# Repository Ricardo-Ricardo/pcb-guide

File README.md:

# pcb-guide
 first keyboard pcb

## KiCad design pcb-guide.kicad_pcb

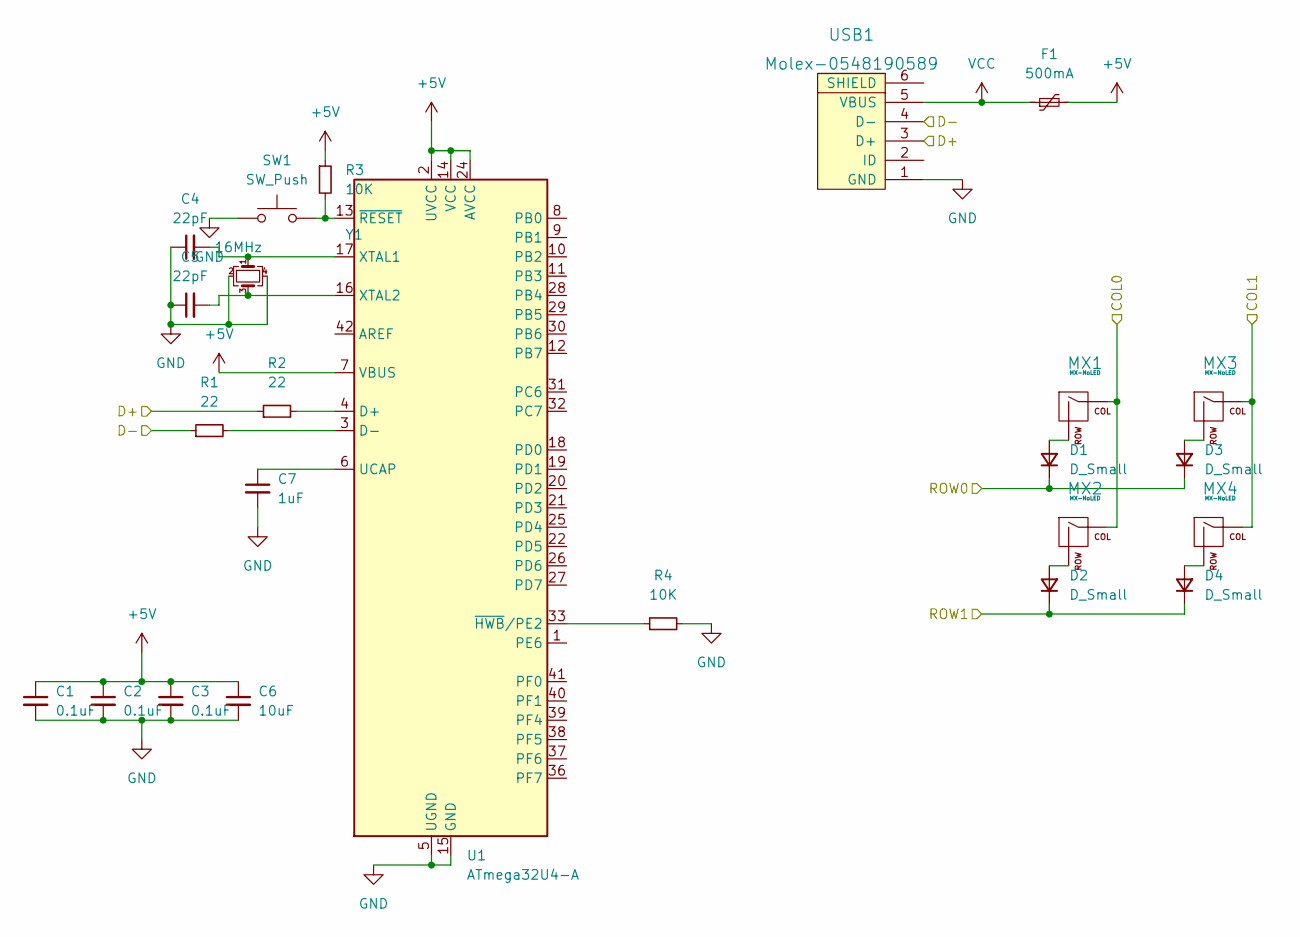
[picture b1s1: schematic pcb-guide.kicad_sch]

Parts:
C1, C2, C3: 0.1uF; C_0805_2012Metric
C4, C5: 22pF; C_0805_2012Metric
C6: 10uF; C_0805_2012Metric
C7: 1uF; C_0805_2012Metric
D1, D2, D3, D4: D_Small; D_SOD-123
F1: 500mA; Fuse_1206_3216Metric
MX1, MX2, MX3, MX4: MX-NoLED; MX-1U
R1, R2: 22; R_0805_2012Metric
R3, R4: 10K; R_0805_2012Metric
SW1: SW_Push; SKQG-1155865
U1: ATmega32U4-A; TQFP-44_10x10mm_P0.8mm
USB1: Molex-0548190589
Y1: 16MHz; TQFP-44_10x10mm_P0.8mm

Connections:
+5V: C1.1, C2.1, C3.1, C6.1, F1.2, R3.1, U1.2 (UVCC), U1.7 (VBUS), U1.14 (VCC), U1.24 (AVCC), U1.34 (VCC), U1.44 (AVCC)
/COL0: MX1.1 (COL), MX2.1 (COL), U1.29 (PB5)
/COL1: MX3.1 (COL), MX4.1 (COL), U1.28 (PB4)
/D+: R2.1, USB1.3 (D+); also elsewhere on the board
/D-: R1.1, USB1.4 (D-); also elsewhere on the board
/ROW0: D1.1 (K), D3.1 (K), U1.27 (PD7)
/ROW1: D2.1 (K), D4.1 (K), U1.30 (PB6)
GND: C1.2, C2.2, C3.2, C4.1, C5.1, C6.2, C7.2, R4.2, SW1.1, U1.5 (UGND), U1.15 (GND), U1.23 (GND), U1.35 (GND), U1.43 (GND), USB1.1 (GND), Y1.2, Y1.4; also elsewhere on the board
unnamed: C4.2, U1.17 (XTAL1), Y1.1
unnamed: C5.2, U1.16 (XTAL2), Y1.3
unnamed: C7.1, U1.6 (UCAP)
unnamed: D1.2 (A), MX1.2 (ROW)
unnamed: D2.2 (A), MX2.2 (ROW)
unnamed: D3.2 (A), MX3.2 (ROW)
unnamed: D4.2 (A), MX4.2 (ROW)
unnamed: R1.2, U1.3 (D-)
unnamed: R2.2, U1.4 (D+)
unnamed: R3.2, SW1.2, U1.13 (~RESET)
unnamed: R4.1, U1.33 (~HWB/PE2)
VCC: F1.1, USB1.5 (VBUS); also elsewhere on the board

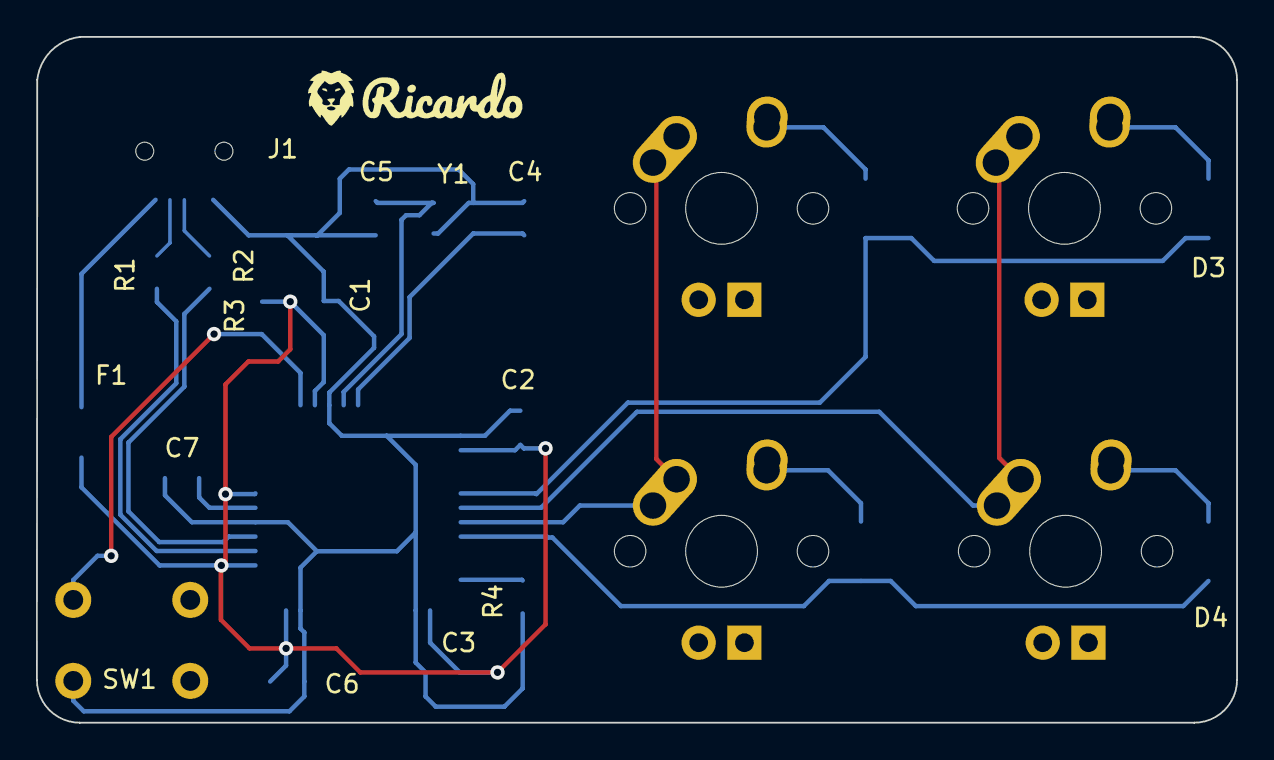
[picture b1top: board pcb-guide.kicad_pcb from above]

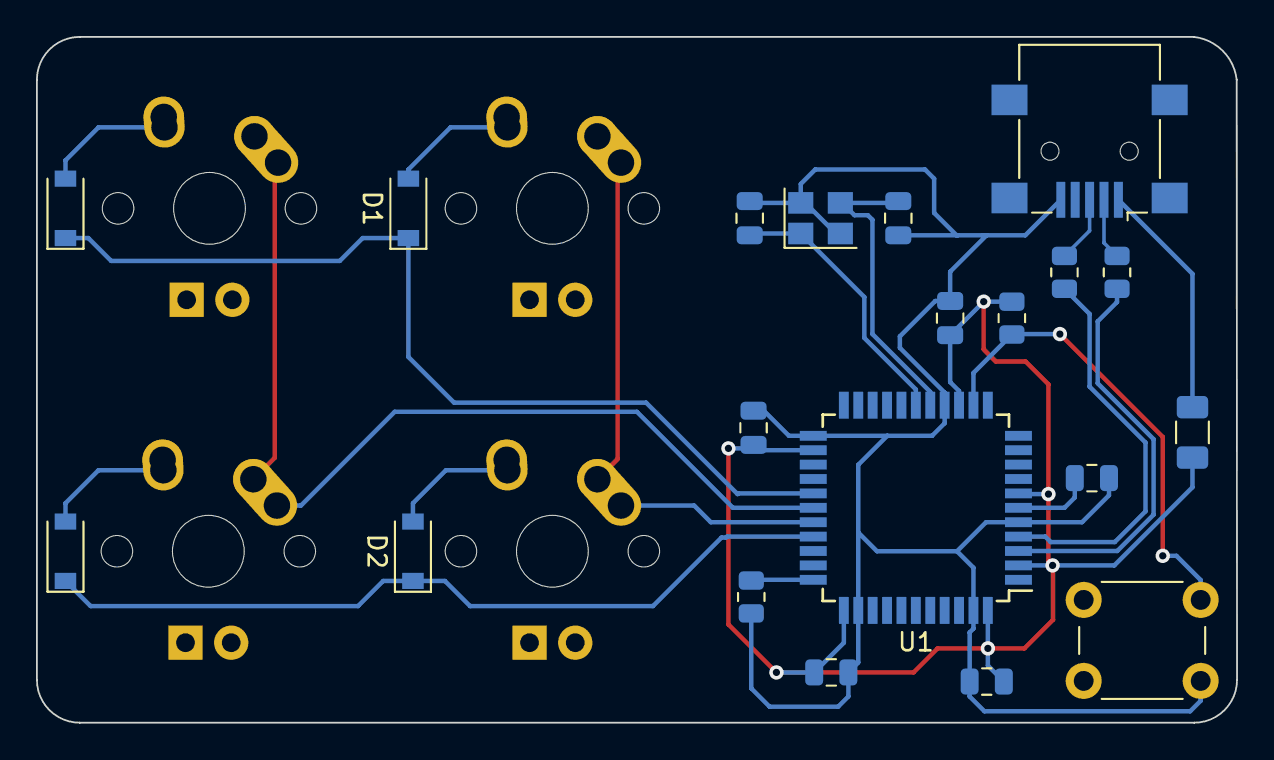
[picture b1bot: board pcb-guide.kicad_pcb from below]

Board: 2 copper layers, 66.7 x 38.1 mm, 24 parts (20 on the bottom side), 20 nets.

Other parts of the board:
J1: USB_B_Mini; USB_Mini-B_Lumberg_2486_01_Horizontal

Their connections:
/D+: J1.3 (D+); also elsewhere on the board
/D-: J1.2 (D-); also elsewhere on the board
GND: J1.5 (GND); also elsewhere on the board
VCC: J1.1 (VBUS); also elsewhere on the board

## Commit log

2022-10-17 Add submodules
2022-10-17 Add footprint libraries
2022-10-17 Atmega32U4 library
2022-10-17 Beginning the schematic
2022-10-17 Schematic and Footprint Bindings
2022-10-17 Creating the PCB
